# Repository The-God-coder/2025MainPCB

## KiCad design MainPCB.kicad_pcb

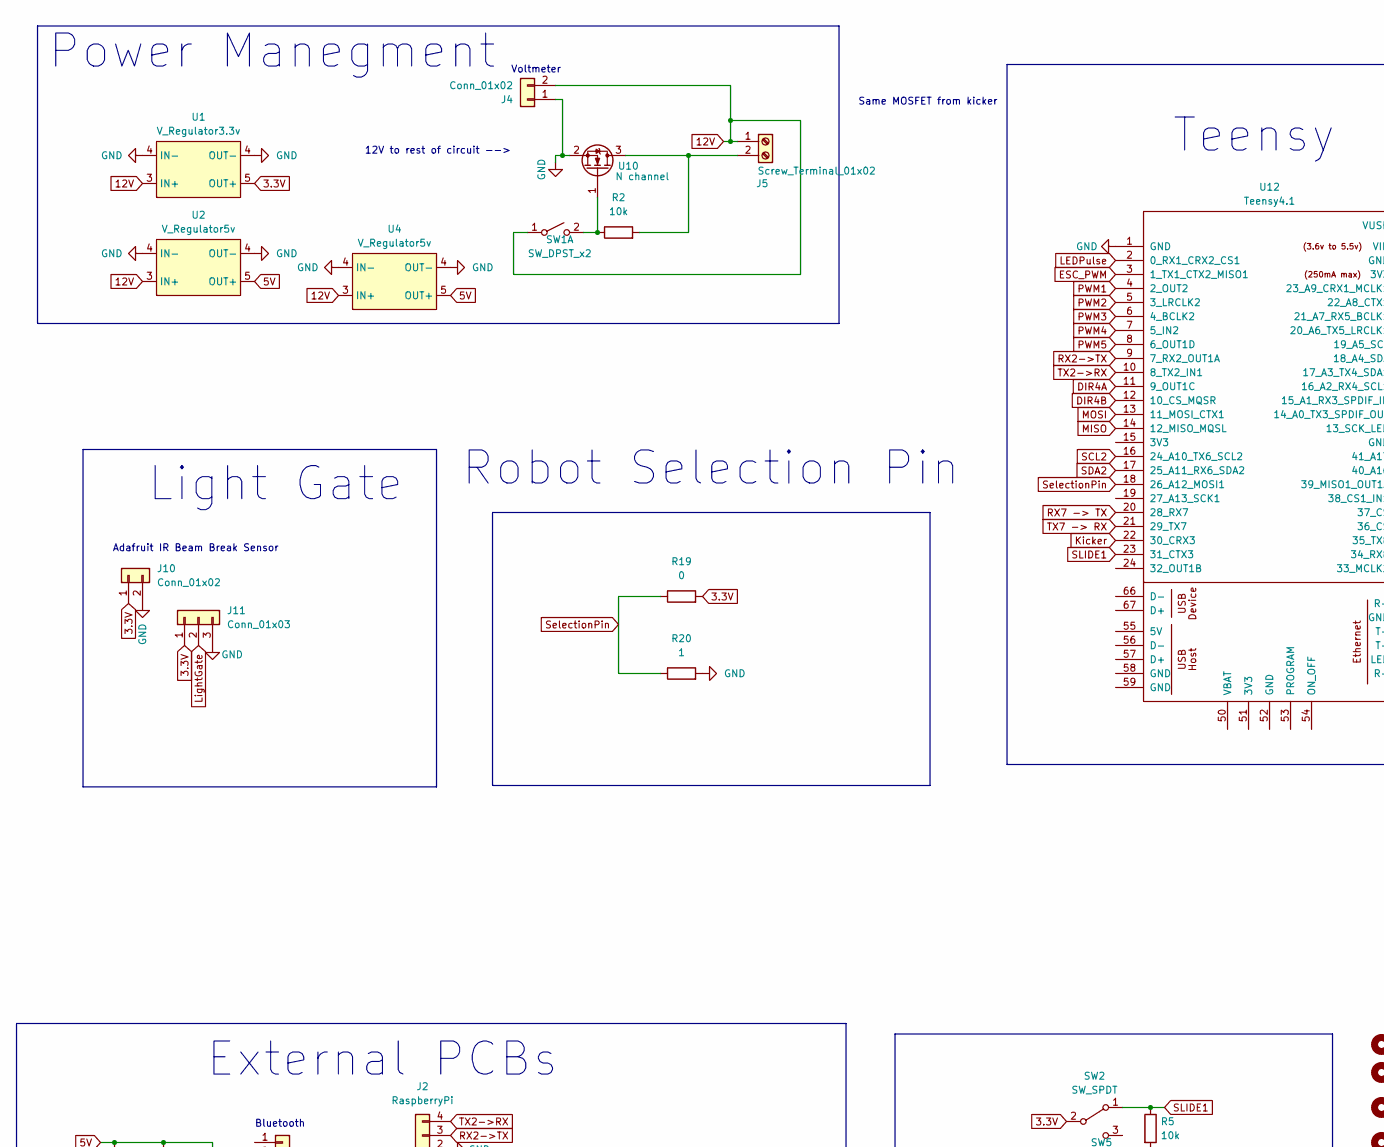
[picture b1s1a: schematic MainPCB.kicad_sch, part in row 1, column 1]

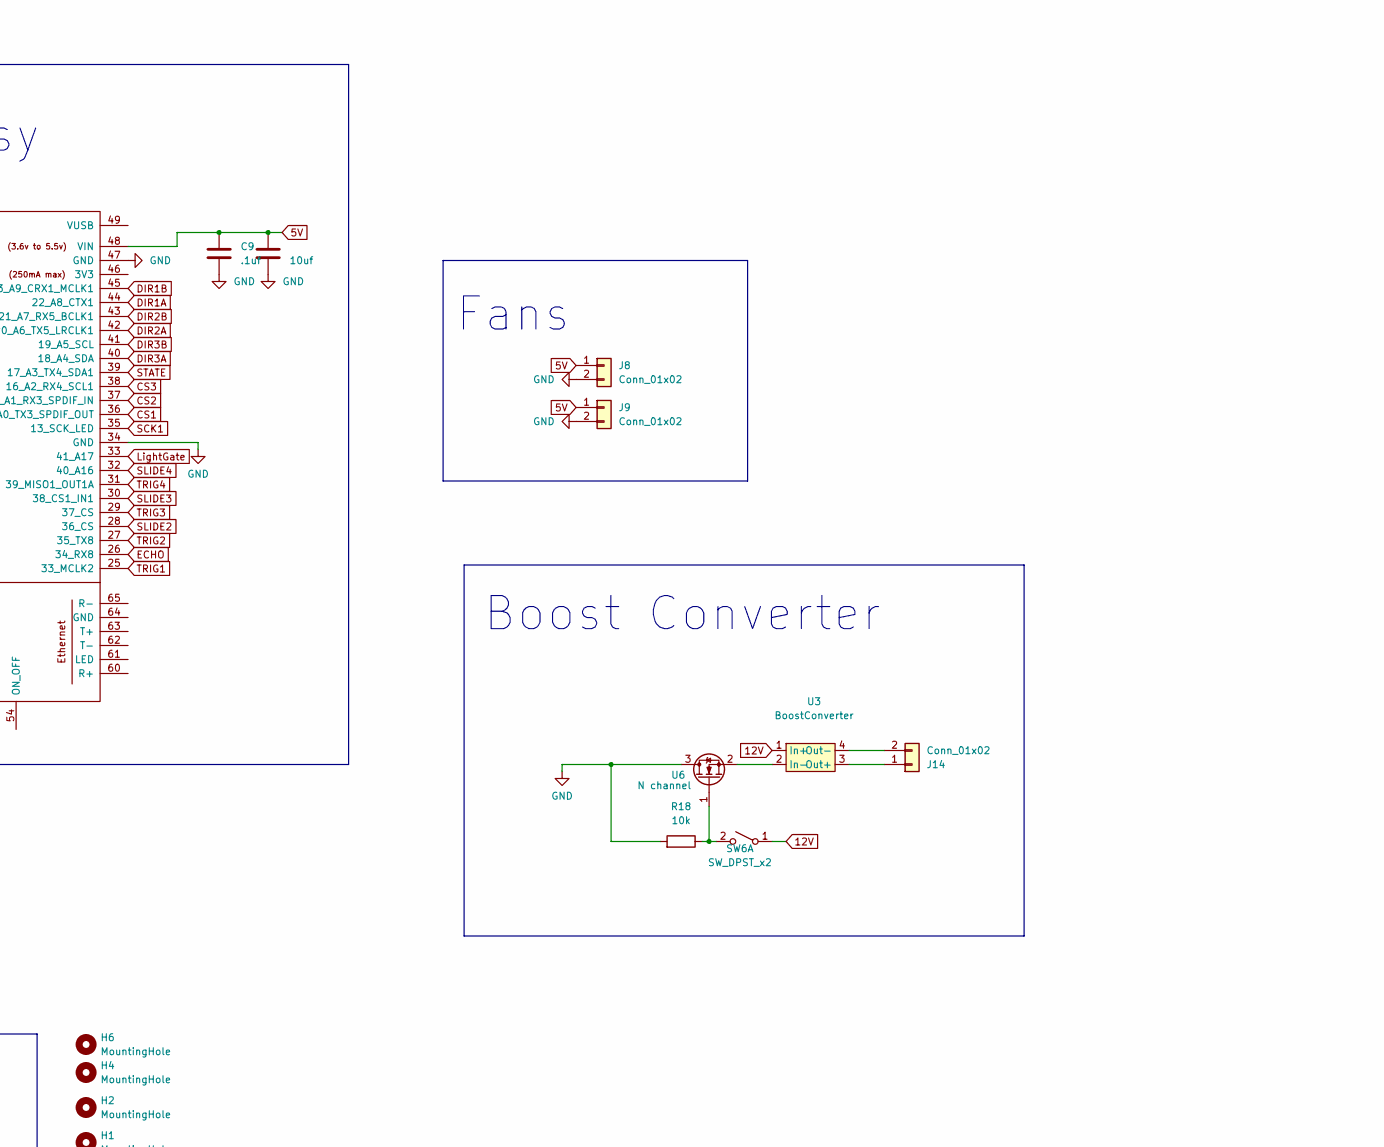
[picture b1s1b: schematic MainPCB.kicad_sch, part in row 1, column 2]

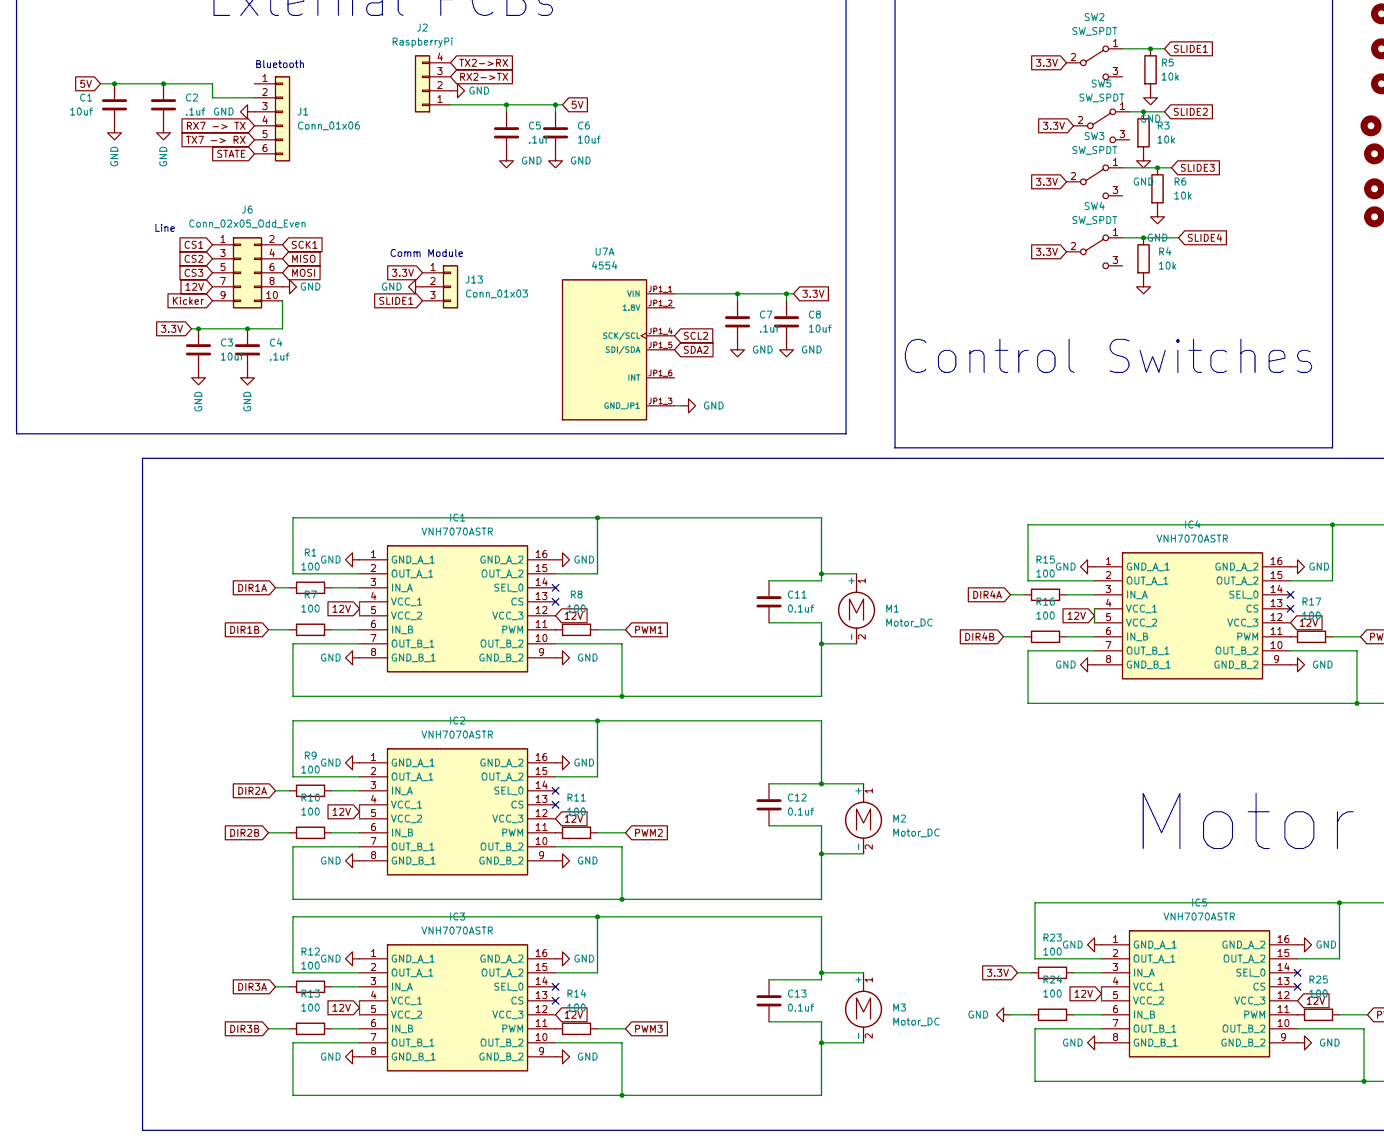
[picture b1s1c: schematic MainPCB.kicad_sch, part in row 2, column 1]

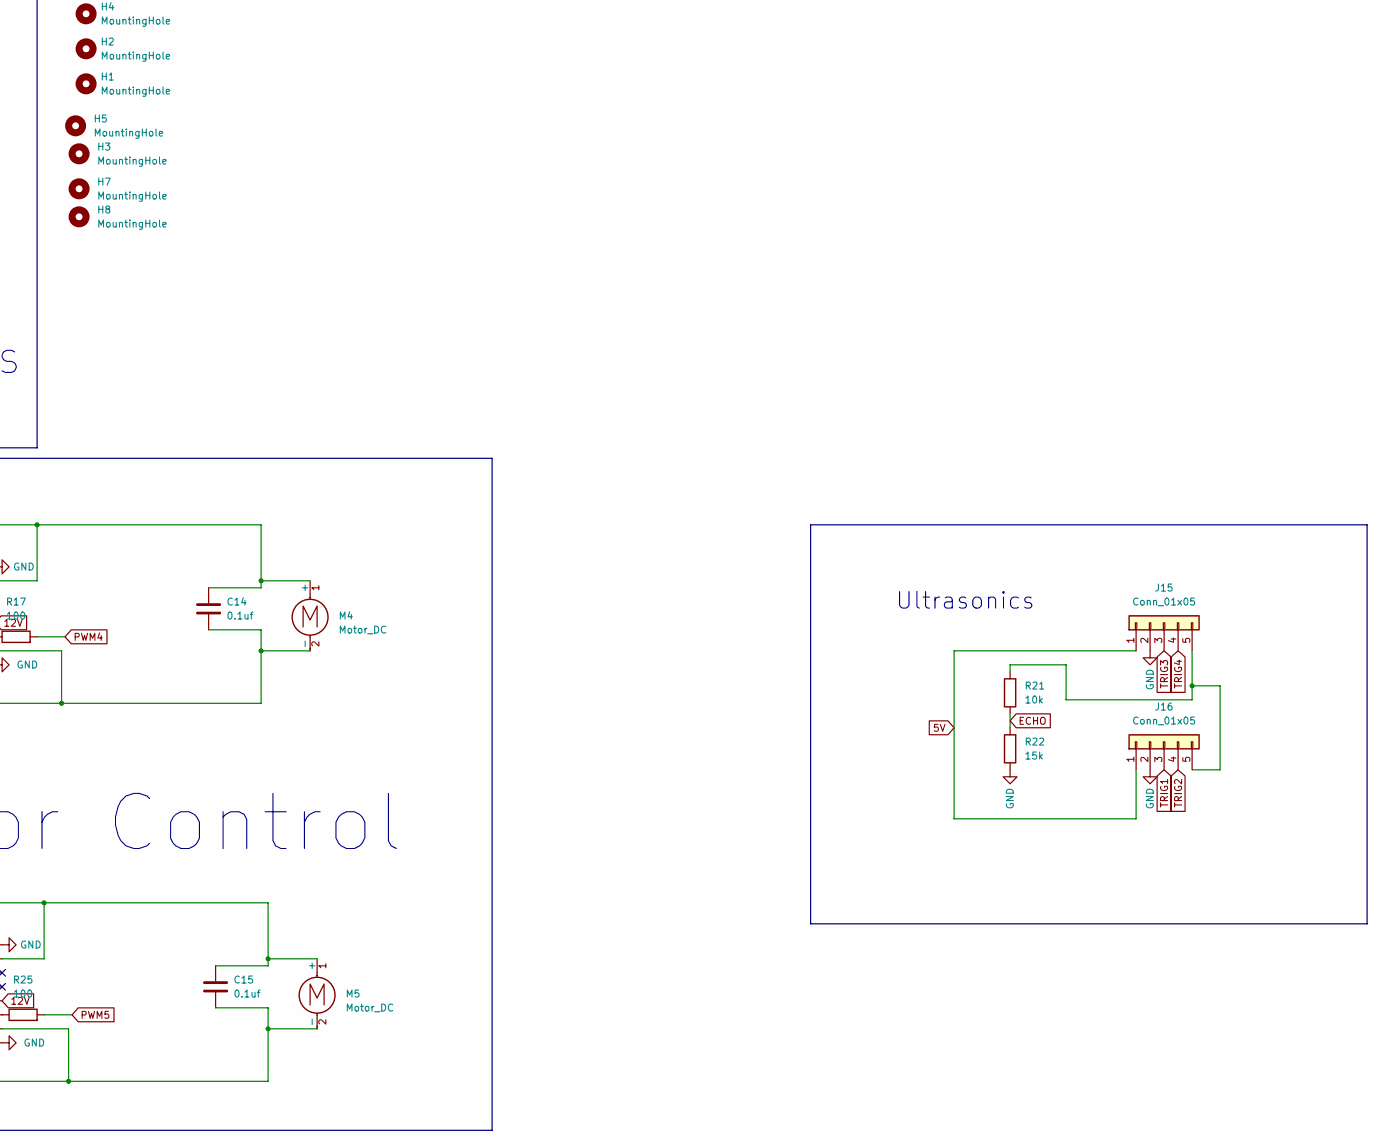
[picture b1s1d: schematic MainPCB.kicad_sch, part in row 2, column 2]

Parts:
C1, C3, C6, C8, C10: 10uf; C_0805_2012Metric
C2, C4, C5, C7, C9: .1uf; C_0805_2012Metric
C11, C12, C13, C14, C15: 0.1uf; C_0805_2012Metric_Pad1.18x1.45mm_HandSolder
H1, H2, H4, H6: MountingHole; MountingHole_2.7mm_M2.5_DIN965_Pad
H3, H5, H7, H8: MountingHole; MountingHole_3.2mm_M3_DIN965_Pad
IC1, IC2, IC3, IC4, IC5: VNH7070ASTR; SOIC127P600X175-16N; Mouser Part Number 511-VNH7070ASTR
J1: Conn_01x06; PinHeader_1x06_P2.54mm_Vertical
J2: RaspberryPi; JST_XH_B4B-XH-AM_1x04_P2.50mm_Vertical
J4: Conn_01x02; PinHeader_2x01_P2.54mm_Vertical
J5: Screw_Terminal_01x02; AMASS_XT60PW-F_1x02_P7.20mm_Horizontal
J6: Conn_02x05_Odd_Even; IDC-Header_2x05_P2.54mm_Vertical
J8, J9, J10: Conn_01x02; PinHeader_1x02_P2.54mm_Vertical
J11, J13: Conn_01x03; PinHeader_1x03_P2.54mm_Vertical
J14: Conn_01x02; JST_XH_B2B-XH-A_1x02_P2.50mm_Vertical
J15, J16: Conn_01x05; JST_XH_B5B-XH-A_1x05_P2.50mm_Vertical
M1, M2, M3, M4, M5: Motor_DC; JST_XH_B2B-XH-AM_1x02_P2.50mm_Vertical
R1, R7, R8, R9, R10, R11, R12, R13, R14, R15, R16, R17, R23, R24, R25: 100; R_0805_2012Metric_Pad1.20x1.40mm_HandSolder
R2, R3, R4, R5, R6, R18: 10k; C_0805_2012Metric_Pad1.18x1.45mm_HandSolder
R19: 0; R_0805_2012Metric_Pad1.20x1.40mm_HandSolder
R20: 1; R_0805_2012Metric_Pad1.20x1.40mm_HandSolder
R21: 10k; C_0805_2012Metric
R22: 15k; C_0805_2012Metric
SW1, SW6: SW_DPST_x2; SPDT_OS102011_CNK
SW2, SW3, SW4, SW5: SW_SPDT; SPDT_OS102011_CNK
U1: V_Regulator3.3v; Pololu Regulator
U2: V_Regulator5v; Pololu5V3.4A
U3: BoostConverter; Boost_Convertor_LM2577
U4: V_Regulator5v; Pololu Regulator
U6, U10: N channel; TO-220-3_Vertical
U7: 4554; MODULE_4554; PARTREV N/A
U12: Teensy4.1; Teensy41

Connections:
3.3V: C3.1, C4.1, C7.1, C8.1, J6.10, J10.1, J11.1, J13.1, R19.2, R23.1, SW2.2 (B), SW3.2 (B), SW4.2 (B), SW5.2 (B), U1.5 (OUT+), U7.JP1_1 (VIN)
5V: C1.1, C2.1, C5.1, C6.1, C9.1, C10.1, J1.2, J2.1, J8.1, J9.1, J15.1, J16.1, U2.5 (OUT+), U4.5 (OUT+), U12.48 (VIN)
12V: IC1.4 (VCC_1), IC1.5 (VCC_2), IC1.12 (VCC_3), IC2.4 (VCC_1), IC2.5 (VCC_2), IC2.12 (VCC_3), IC3.4 (VCC_1), IC3.5 (VCC_2), IC3.12 (VCC_3), IC4.4 (VCC_1), IC4.5 (VCC_2), IC4.12 (VCC_3), IC5.4 (VCC_1), IC5.5 (VCC_2), IC5.12 (VCC_3), J4.2, J5.1, J6.7, SW1.1 (A), SW6.1 (A), U1.3 (IN+), U2.3 (IN+), U3.1 (In+), U4.3 (IN+)
CS1: J6.1, U12.36 (14_A0_TX3_SPDIF_OUT)
CS2: J6.3, U12.37 (15_A1_RX3_SPDIF_IN)
CS3: J6.5, U12.38 (16_A2_RX4_SCL1)
DIR1A: R1.1, U12.44 (22_A8_CTX1)
DIR1B: R7.1, U12.45 (23_A9_CRX1_MCLK1)
DIR2A: R9.1, U12.42 (20_A6_TX5_LRCLK1)
DIR2B: R10.1, U12.43 (21_A7_RX5_BCLK1)
DIR3A: R12.1, U12.40 (18_A4_SDA)
DIR3B: R13.1, U12.41 (19_A5_SCL)
DIR4A: R15.1, U12.11 (9_OUT1C)
DIR4B: R16.1, U12.12 (10_CS_MQSR)
ECHO: R21.1, R22.2, U12.26 (34_RX8)
ESC_PWM: U12.3 (1_TX1_CTX2_MISO1)
GND: C1.2, C2.2, C3.2, C4.2, C5.2, C6.2, C7.2, C8.2, C9.2, C10.2, IC1.1 (GND_A_1), IC1.8 (GND_B_1), IC1.9 (GND_B_2), IC1.16 (GND_A_2), IC2.1 (GND_A_1), IC2.8 (GND_B_1), IC2.9 (GND_B_2), IC2.16 (GND_A_2), IC3.1 (GND_A_1), IC3.8 (GND_B_1), IC3.9 (GND_B_2), IC3.16 (GND_A_2), IC4.1 (GND_A_1), IC4.8 (GND_B_1), IC4.9 (GND_B_2), IC4.16 (GND_A_2), IC5.1 (GND_A_1), IC5.8 (GND_B_1), IC5.9 (GND_B_2), IC5.16 (GND_A_2), J1.3, J2.2, J4.1, J6.8, J8.2, J9.2, J10.2, J11.3, J13.2, J15.2, J16.2, R3.2, R4.2, R5.2, R6.2, R18.2, R20.2, R22.1, R24.1, U1.4 (IN-), U2.4 (IN-), U4.4 (OUT-), U6.3 (D), U7.JP1_3 (GND_JP1), U10.2 (S), U12.1 (GND), U12.34 (GND), U12.47 (GND)
Kicker: J6.9, U12.22 (30_CRX3)
LEDPulse: U12.2 (0_RX1_CRX2_CS1)
LightGate: J11.2, U12.33 (41_A17)
MISO: J6.4, U12.14 (12_MISO_MQSL)
MOSI: J6.6, U12.13 (11_MOSI_CTX1)
unnamed: IC1.3 (IN_A), R1.2
unnamed: IC1.6 (IN_B), R7.2
unnamed: C11.1, IC1.2 (OUT_A_1), IC1.15 (OUT_A_2), M1.1 (+)
unnamed: C11.2, IC1.7 (OUT_B_1), IC1.10 (OUT_B_2), M1.2 (-)
unnamed: IC1.11 (PWM), R8.1
unnamed: IC2.3 (IN_A), R9.2
unnamed: IC2.6 (IN_B), R10.2
unnamed: C12.1, IC2.2 (OUT_A_1), IC2.15 (OUT_A_2), M2.1 (+)
unnamed: C12.2, IC2.7 (OUT_B_1), IC2.10 (OUT_B_2), M2.2 (-)
unnamed: IC2.11 (PWM), R11.1
unnamed: IC3.3 (IN_A), R12.2
unnamed: IC3.6 (IN_B), R13.2
unnamed: C13.1, IC3.2 (OUT_A_1), IC3.15 (OUT_A_2), M3.1 (+)
unnamed: C13.2, IC3.7 (OUT_B_1), IC3.10 (OUT_B_2), M3.2 (-)
unnamed: IC3.11 (PWM), R14.1
unnamed: IC4.3 (IN_A), R15.2
unnamed: IC4.6 (IN_B), R16.2
unnamed: C14.1, IC4.2 (OUT_A_1), IC4.15 (OUT_A_2), M4.1 (+)
unnamed: C14.2, IC4.7 (OUT_B_1), IC4.10 (OUT_B_2), M4.2 (-)
unnamed: IC4.11 (PWM), R17.1
unnamed: IC5.3 (IN_A), R23.2
unnamed: IC5.6 (IN_B), R24.2
unnamed: C15.1, IC5.2 (OUT_A_1), IC5.15 (OUT_A_2), M5.1 (+)
unnamed: C15.2, IC5.7 (OUT_B_1), IC5.10 (OUT_B_2), M5.2 (-)
unnamed: IC5.11 (PWM), R25.1
unnamed: J5.2, R2.2, U10.3 (D)
unnamed: J14.1, U3.3 (Out+)
unnamed: J14.2, U3.4 (Out-)
unnamed: J15.5, J16.5, R21.2
unnamed: R2.1, SW1.2 (B), U10.1 (G)
unnamed: R18.1, SW6.2 (B), U6.1 (G)
unnamed: U3.2 (In-), U6.2 (S)
PWM1: R8.2, U12.4 (2_OUT2)
PWM2: R11.2, U12.5 (3_LRCLK2)
PWM3: R14.2, U12.6 (4_BCLK2)
PWM4: R17.2, U12.7 (5_IN2)
PWM5: R25.2, U12.8 (6_OUT1D)
RX2->TX: J2.3, U12.9 (7_RX2_OUT1A)
RX7 -> TX: J1.4, U12.20 (28_RX7)
SCK1: J6.2, U12.35 (13_SCK_LED)
SCL2: U7.JP1_4 (SCK/SCL), U12.16 (24_A10_TX6_SCL2)
SDA2: U7.JP1_5 (SDI/SDA), U12.17 (25_A11_RX6_SDA2)
SLIDE1: J13.3, R5.1, SW2.1 (A), U12.23 (31_CTX3)
SLIDE2: R3.1, SW5.1 (A), U12.28 (36_CS)
SLIDE3: R6.1, SW3.1 (A), U12.30 (38_CS1_IN1)
SLIDE4: R4.1, SW4.1 (A), U12.32 (40_A16)
STATE: J1.6, U12.39 (17_A3_TX4_SDA1)
SelectionPin: R19.1, R20.1, U12.18 (26_A12_MOSI1)
TRIG1: J16.3, U12.25 (33_MCLK2)
TRIG2: J16.4, U12.27 (35_TX8)
TRIG3: J15.3, U12.29 (37_CS)
TRIG4: J15.4, U12.31 (39_MISO1_OUT1A)
TX2->RX: J2.4, U12.10 (8_TX2_IN1)
TX7 -> RX: J1.5, U12.21 (29_TX7)

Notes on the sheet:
Ultrasonics
Control Switches
Light Gate
Voltmeter
External PCBs
Fans
Line
Bluetooth
Same MOSFET from kicker
Adafruit IR Beam Break Sensor
Power Manegment
Boost Converter
Teensy
12V to rest of circuit -->
Robot Selection Pin
Motor Control
Comm Module

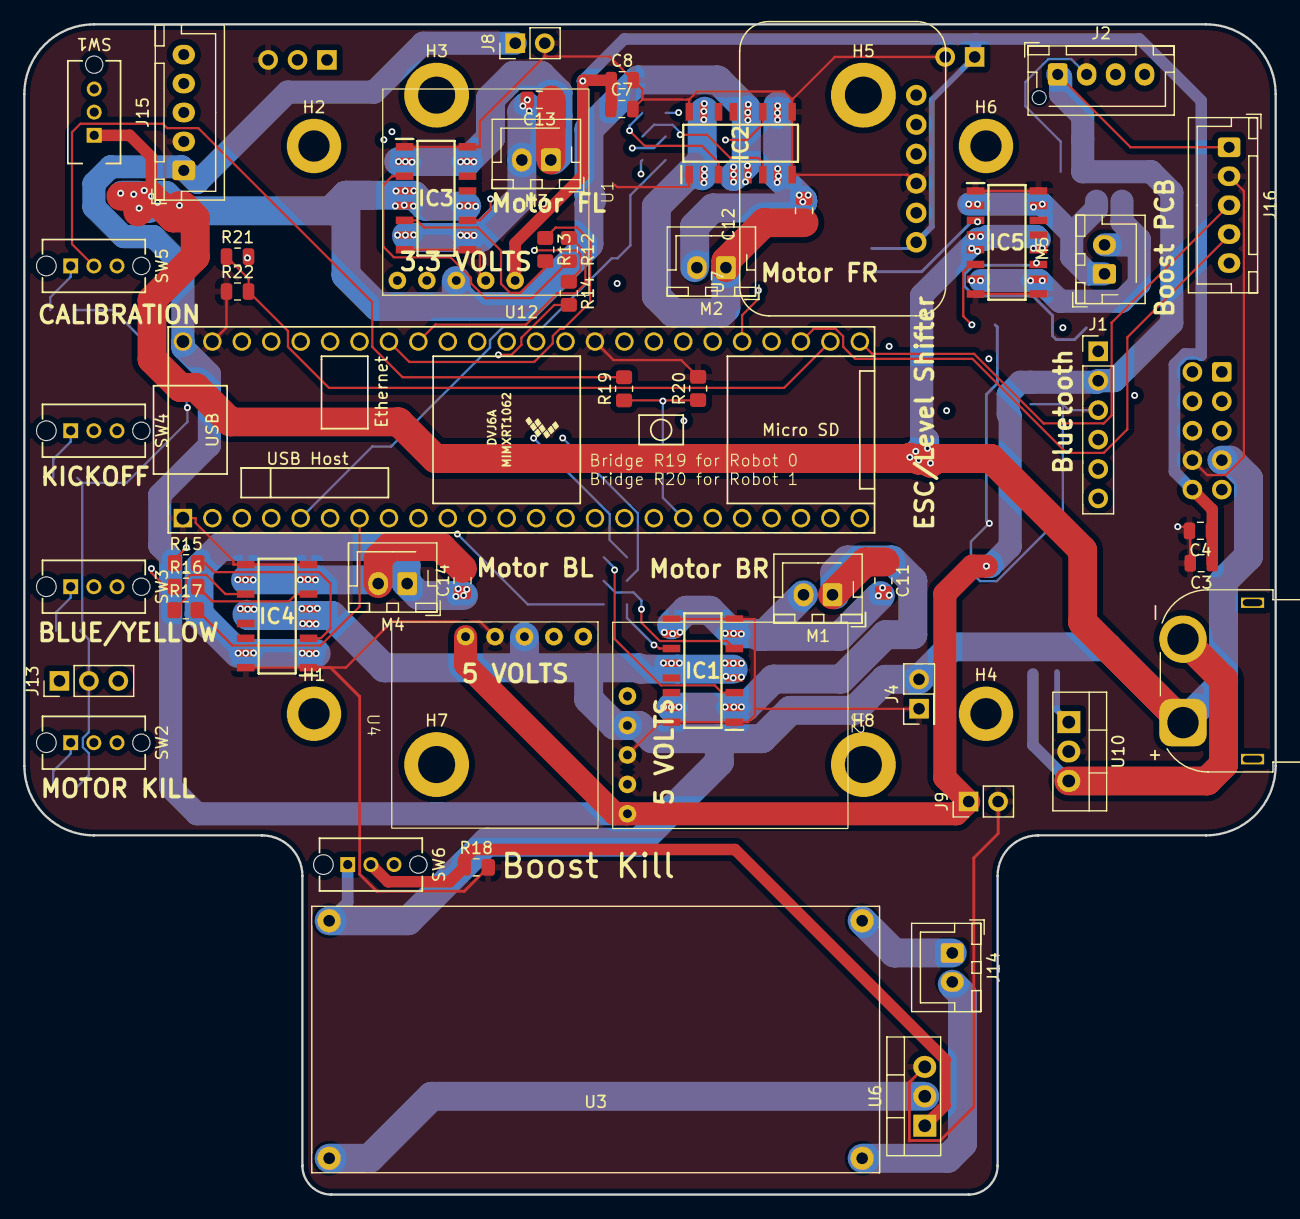
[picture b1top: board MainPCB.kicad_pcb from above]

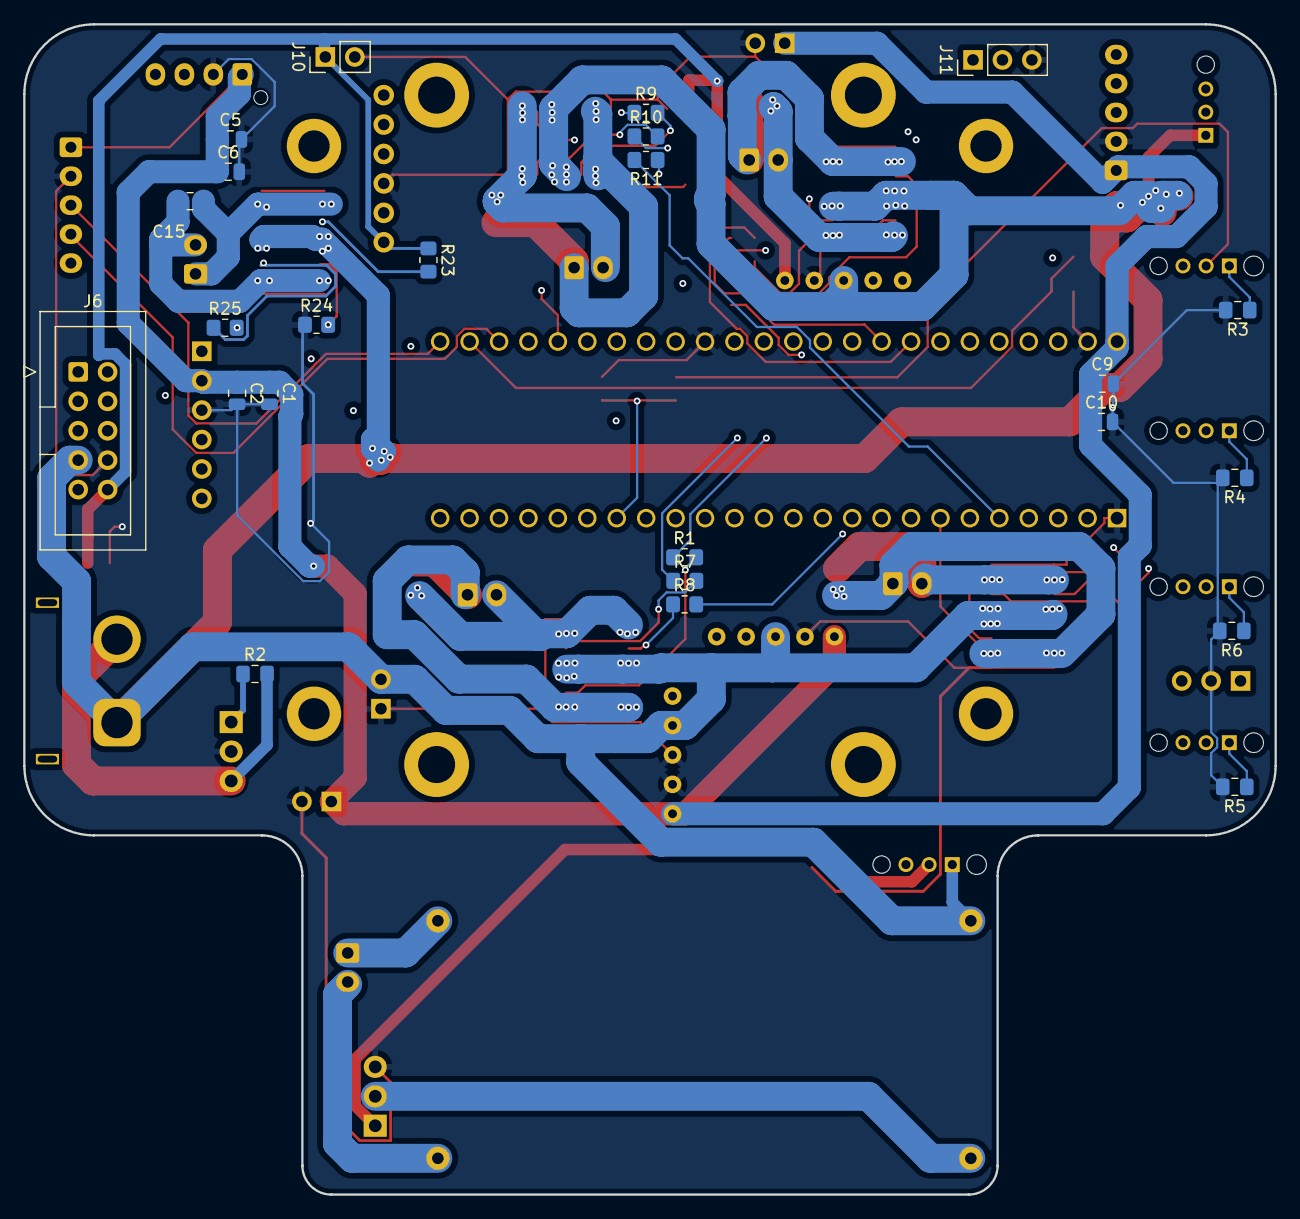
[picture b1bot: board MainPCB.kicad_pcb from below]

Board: 4 copper layers, 108.0 x 101.0 mm, 85 parts (24 on the bottom side), 74 nets.

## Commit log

2024-11-10 Finished Power Wiring
2024-11-10 Finished Main PCB
2024-11-10 Closed Kicad to fix locks
2024-11-10 Fixed Holes error
2024-11-15 Changed Top Plate Sketch
2025-01-08 Added Boost Converter
2025-01-10 Flipped JST Motor Connectors
2025-03-08 changed a lot
